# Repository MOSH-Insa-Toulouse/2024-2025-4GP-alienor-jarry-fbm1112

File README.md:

# 2024-2025-4GP - Projet Capteur low-tech Graphite - Aliénor Jarry et Bastien Maïs

## Sommaire :
- [Contexte](#contexte)
- [Livrables](#livrables)
- [Matériel nécessaire](#matériel-nécessaire)
- [1. Simulation électronique du capteur sous LTSpice](#1-simulation-électronique-du-capteur-sous-ltspice)
- [2. Design du PCB sous KiCad](#2-design-du-pcb-sous-kicad)
- [3. Réalisation du Shield](#3-réalisation-du-shield)
- [4. Code Arduino](#4-code-arduino)
- [5. Application Android APK sous MIT App Inventor](#5-application-android-apk-sous-mit-app-inventor)
- [6. Banc de test](#6-banc-de-test)
- [7. Datasheet du capteur](#7-datasheet-du-capteur)
- [Conclusion](#conclusion)
- [Contacts](#contacts)

## Contexte
Dans le cadre de l'UF "Du capteur au banc de test en open source hardware" se déroulant lors de notre 4ème année Génie Physique à l'INSA de Toulouse, nous avons développé un capteur à jauge de contrainte low-tech à base de crayon graphite. Ce projet repose sur le rapport scientifique "Pencil Drawn Strain Gauges and Chemiresistors on Paper", publié en 2014 par Cheng-Wei Lin*, Zhibo Zhao*, Jaemyung Kim & Jiaxing Huang.

Le capteur se compose uniquement d'un morceau de papier sur laquelle une trace de crayon à papier dépose une fine couche de graphite. Un dépôt de graphite sur du papier constitue un système granulaire, où des grains de tailles variables sont séparés par une distance appelée distance inter-grain. La conductance suit une loi exponentielle décroissante en fonction de la distance inter-grain, laquelle peut être modifiée en déformant le papier. Plus la distance inter-grain augmente, plus la conductance diminue. Dans ce cas, la résistance devient très élevée, car conductance et résistance sont inversement proportionnelles. Ainsi, la contrainte exercée sur le matériau peut être déterminée en mesurant simplement la résistance aux bornes du capteur.

L'objectif est de concevoir un dispositif permettant la mesure de déformation à partir d'un capteur low-tech, puis d'évaluer ses performances en le comparant à un capteur commercial.

## Livrables
- Un Shield PCB branchée sur une carte Arduino UNO, intégrant un capteur graphite, un amplificateur de transimpédance et un module Bluetooth. Idéalement, il incluerait également un écran OLED, un encodeur rotatif, un potentiomètre numérique (remplaçant la résistance R2 dans le circuit amplificateur), ainsi qu'un connecteur pour un servomoteur et un capteur de flexion (afin de comparer ses mesures avec celles du capteur en graphite).
- Un code Arduino garantissant la gestion de tous les composants et l'acquisition des mesures (mesures de contrainte, échanges via Bluetooth, affichage OLED, encodeur rotatif, potentiomètre numérique et servomoteur).
- Une application APK Android qui gère l'interface entre le PCB et le code Arduino. L'application doit au minimum afficher la valeur de la résistance de la jauge de contrainte ainsi que sa variation relative sur le smartphone.
- Un code Arduino dédié au banc de test pour la mesure de la jauge de contrainte.
- Une datasheet du capteur en graphite (incluant le circuit de transimpédance).

## Matériel nécessaire
Pour concevoir notre dispositif électronique, voici la liste des composants nécessaires :
- Des résistances : 1 de 1 kΩ, 1 de 10 kΩ, 2 de 100 kΩ pour l'amplificateur transimpédance. 1 de 47 kΩ pour le flex sensor (capteur commercial)
- Des condensateurs : 2 de 100 nF et 1 de 1 μF pour l'amplificateur transimpédance. 1 de 100 nF pour l'encodeur rotatif
- Un amplificateur opérationnel LTC1050
- Un potentiomère numérique MCP41050
- Une carte Arduino UNO
- Un module Bluetooth HC05
- Un écran OLED 128×64
- Un encodeur rotatif
- Un servomoteur
- Un flex sensor
- Un morceau de papier et crayon pour la fabrication du capteur graphite

## 1. Simulation électronique du capteur sous LTSpice

Notre capteur graphite présente une résistance variable de l’ordre du gigaohm (GΩ). Lorsque une tension de 5V est appliquée à ses bornes, un courant extrêmement faible est généré, de l’ordre de 100 nA en moyenne.

Un tel signal est difficilement exploitable sans amplification. Pour y remédier, nous avons utilisé un montage transimpédance basé sur un amplificateur opérationnel (AOP). Ce montage permet de convertir ce courant en une tension suffisamment élevée pour être lue par le convertisseur analogique-numérique (ADC) d’une carte Arduino UNO. 

**Nous avons simulé ce montage à l’aide du logiciel LTspice, voici notre schéma du circuit analogique** : 

Nous avons choisi l'AOP LTC1050 car il est adapté pour traiter de très faibles courants d'entrée. Son faible offset de tension assure une conversion précise du courant en tension.

**Deux éléments de simulation sont intégrés au circuit** :

- 🟥 Simulation du capteur  
- 🟪 Simulation du bruit

De plus, des filtres ont été ajoutés au montage afin d'atténuer les perturbations indésirables (par ex : bruits d'alimentation à 50 Hz) 

**Trois filtres assurant le traitement du signal** :

- 🟩 Filtre en entrée de l'AOP(R2, C1) :  
 C'est un filtre passe-bas passif de fréquence de coupure fc = 16 Hz. Il filtre les bruits en courant sur le signal d'entrée.

- 🟦Filtre couplé à l'AOP (R4, C2) :  
  C'est un filtre passe-bas actif avec fc = 1,6 Hz. Il filtre la composante du bruit à 50Hz du réseau électrique.

- 🟨 Filtre en sortie de l'AOP (R5, C4) :  
  C'est un filtre passe-bas passif avec fc = 1,6 kHz. Il élimine les parasites générés lors du traitement du signal.

De plus, la résistance R1 en entrée protège contre les décharges électrostatiques. Cette résistance en combinaison avec la capacité C5, forme un filtre pour atténuer les bruits de tension. 

**Voici la réponse de notre circuit afin de vérifier que le capteur est bien amplifié** :

Nous voyons que le signal est amplifié à 1V. Ainsi, l'Arduino UNO pourra le mesurer. 

**Réponse avec un courant alternatif pour vérifier que le bruit est bien filtré** :

Nous remarquons que le bruit est bien atténué à 50 Hz, d'environ 72 dB.

## 2. Design du PCB sous KiCad

Notre PCB a été conçue sur le logigiel Kicad (version 9).

Nous avons tout d'abord réalisé la schématique en reproduisant le circuit transimpédance (en enlevant la partie simulant le bruit). Nous avons  remplacé la résistance R3 par un potentiomètre digital. Cela nous permet d'ajuster le gain de notre AOP en fonctions de nos besoins. Également, nous avons créé les symboles des différents composants/modules intégrés. Ces modules assureront une mesure précise de notre capteur en graphite et permettra de comparer les résultats obtenus.

**Voici le schéma électrique de l'ensemble de notre montage** :

Ensuite, nous avons réalisé les empreintes de nos composants en prenant en compte leurs caractéristiques techniques : nombre de pins, espacement, dimensions, géométrie,...
afin de les placer sur notre PCB. 

Puis, nous sommes allés dans l'onglet "éditeur de PCB" sous Kicad pour designer notre circuit. Nous nous sommes appuyés sur un modèle de carte Arduino Uno. Nous avons ainsi placé nos différents composants, de manière à regouper les composants du circuit transmpédance. De plus les modules, et les composants du circuit transimpédance devaient être placés proches de leurs branchements Arduino respectifs. Nous sommes ensuite passés à la partie routage du circuit. Notre principale difficulté a été d’optimiser le placement des composants afin de limiter au maximum l’utilisation de vias, notamment pour les connexions au GND. Nous avons tout de même trois vias sur notre PCB. Pour garantir une bonne connexion entre toutes les broches GND des composants, nous avons mis en place un plan de masse.

**Voici le résultat final obtenu de notre routage** : 

**Voici le rendu 3D de notre PCB, avec ses différents modules et composants intégrés**:

### **Erreurs réalisées** : 

Nous avons fait quelques erreurs concernant les empreintes de nos modules.

**Servomoteur** :
Nous avons inversé les broches GND et 5V. 

**Bluetooth HC-05** : 
L'empreinte de notre Bluetooth n'est pas correcte. Nous avions mis dans l'ordre la broche VCC, GND, TX, RX, ENABLE et STATE alors que la broche ENABLE est la première. Voici les broches correctes du Bluetooth :

Un conseil serait de se baser sur la datasheet de chaques composant afin de réaliser les empreintes! De plus, il faut faire attention concerant les broches TX et RX du Bluetooth. La broche RX de la carte Arduino doit être raccordée à la broche TX du Bluetooth, et la broche TX du Arduino à la broche RX du Bluetooth.
Nous avons résolu le problème des pins Bluetooth en utilisant des connecteur mâles, femelles permettant de brancher correctement le Bluetooth.

## 3. Réalisation du Shield 

Une fois notre PCB finalisé sous KiCad, nous l’avons envoyé à Cathy afin qu’elle puisse vérifier que le PCB était conforme et prêt pour une impression correcte. Puis, nous avons généré le masque de gravure de notre PCB que Cathy s’est chargée d’imprimer. Ensuite, nous sommes allées avec Cathy au GEI afin de tirer notre PCB.

Nous n’avons pas pu manipuler directement, mais nous avons tout de même pu observer le processus de fabrication de la carte. Cathy a procédé ainsi :

1. Insolation UV de la plaque en époxy recouverte d'une fine couche de cuivre (destinée à recevoir le circuit imprimé) et d'une résine photosensible, à travers le masque, pour durcir la résine dans les zones exposées.
2. Développement : la plaque est plongée dans un révélateur pour éliminer la résine non exposée à la lumière UV, laissant ainsi un motif de résine durcie correspondant au circuit imprimé.
3. Gravure : La plaque est ensuite immergée dans un bain de perchlorure de fer, qui dissout le cuivre non protégé par la résine durcie, formant ainsi les pistes du circuit imprimé.
4. Nettoyage à l’acétone pour éliminer les résidus de résine restants après la gravure.

**Voici une photo du masque de gravure et une photo de notre PCB une fois imprimé** :

**Nous tenions à grandement remercier Cathy pour son aide tout au long du projet, et en particulier pour l'impression de notre PCB.**

### Assemblage du circuit :

Nous avons ensuite procédé au perçage de la plaquette pour permettre l'insertion des différents composants, en veillant à respecter la taille des trous. Un forêt plus petit était nécessaire pour les résistances et les condensateurs. Une fois le perçage effectué, nous avons soudé les composants sur le PCB. Il faut bien faire attention à souder uniquement sur les pastilles, sauf pour les pastilles GND où un débordement est moins problématique, car elles sont toutes reliées au plan de masse. Un excès de soudure sur les pastilles pourrait en effet créer des courts-circuits. De plus, nous avons dû ajouter un fil reliant la broche 5V du flex sensor au 5V du module Bluetooth, car une portion de cuivre sur la piste les reliant a été retirée accidentellement en tentant d’enlever un surplus de soudure.

**Voici une photo de l'assemblage de notre circuit (sans les modules) ainsi qu'une photo de nos soudures** :

## 4. Code Arduino 

Afin de réaliser le code arduino nous avons utilisé l'IDE 2.3.2.

Dans le cadre d'une utilisation d'application mobile nous avons donc utilisé un module bluetooth. Cela a ainsi nécessité d'inclure la librairie SoftwareSerial pour initier la communication entre l'application et le pcb via le module.

Pour une utilisation plus classique de notre montage, l'écran OLED permet l'affichage des valeurs issues des mesures de capteurs de la plaquette impliquant l'utilisation de la librairie Adafruit_SSD1306. Cette librairie est plus délicate à manipuler car gourmande en mémoire RAM. Pour pallier cet effet, il nous est impératif de limiter l'affichage au strict nécessaire afin de contrôler l'utilisation de la RAM et d'éviter d'éventuels disfonctionnements du programme.

Dans le dossier Arduino se trouve le programme complet strucuré qui permet de faire différents types de mesures selon le capteur utilisé (graphite ou flex sensor). Lors du lancement de l'Arduino, le programme effectue une calibration du potentiomètre digital selon la valeur mesurée par le capteur graphite pour ensuite afficher un menu déroulant que l'on peut balayer à l'aide de l'encodeur rotatif.

Le menu affiche 3 choix d'actions possibles : 

- Une mesure instantanée du capteur graphite toutes les 500ms
- Une mesure du flex sensor toutes les 500ms
- Une calibration du potentiomètre digital

Pour sélectionner une action du menu, il suffit de tourner la molette et d'appuyer sur le bouton central de l'encodeur. Si l'on souhaite sortir d'une action du menu, nous tournons simplement la molette de l'encodeur.

Ainsi, on obtient la résistance du capteur graphite avec la formule suivante :

Et dans notre cas, notre résistance R3 est variable : elle est issue du réglage du potentiomètre à l'aide d'une méthode de dichotomie.

Finalement, nous n'avons pas utilisé le servomoteur comme module par manque de temps.

## 5. Application Android APK sous MIT App Inventor
Comme mentionné dans la partie précèdente, une application mobile a été réalisée sous MIT App Inventor.
L'application reçoit les données transmis par le module bluetooth HC-05 puis affiche la valeur reçue en Mohm pour le capteur graphite ou en ohms pour le flex sensor.

## 6. Banc de test
Pour spécifier notre capteur graphite et son montage transimpédance, nous avons utilisé le banc de test fabriqué par le binôme Maëlys et Arthur. Un grand merci à eux de nous avoir prêter leur banc de test. Ce banc de test comporte des demis-cercles avec des diamètres différents allant de 2cm à 4,5cm avec un rajout de 0,5cm entre chaque demi-cercle. Au total, il y a 6 demi-cercles. Ce banc de test comporte des encoches pour chaque demi-cercle qui permet d'insérer facilement le capteur. Une fois le capteur mis dans l'une de ses encoches, il est plus aisé d'appliquer une flexion ou une compression sur le capteur. La capteur se déforme en suivant la courbure du demi-cercle. Ainsi, nous appliquons une contrainte qui provoque une variation de la résistance du capteur. Nous allons mesurer cette contrainte en fonction de la déformation.

La variation relative de la résistance se définit par : ΔR/R0 (avec R0 la résistance initiale du capteur avant sa déformation et ΔR la variation de la résistance après et avant déformation). La déformation est : ε=e/D (avec e=0,2mm l'épaisseur du papier utilisé et D le diamètre du demi-cercle). Nous avons donc une déformation variant de 0.004 pour le plus grand demi-cerle à 0.01 pour le plus petit. Il faut faire attention à bien mettre les diamètres des demi-cercles en mm! 

**Voici le banc de test que nous avons utilisé :**

### Voici les courbes caractéristiques pour des crayons F, HB et B en flexion et en compression :

### Voici le graphe comparant le Flex Sensor et le capteur Graphite pour F, HB et B (en flexion) :

**Interprétation des courbes et comparaison avec la théorie :**

Nous remarquons que la résistance augmente lorsque nous mettons le capteur en flexion et que la résistance diminue lors de la compression de ce dernier. Ce phénomène est tout à fait attendu : en théorie, lorsqu’on soumet le capteur à une flexion, la monocouche de graphite déposée sur le papier s’étire, augmentant la distance entre les atomes de carbone. Cette augmentation de distance entraîne une hausse de la résistance du capteur. À l’inverse, en compression, les atomes de carbone se rapprochent, entraînant une diminution de la résistance.

Nous remarquons que les variations relatives ne sont pas les mêmes en fonction de la dureté du crayon utilisé. 
Plus le crayon est gras :  9H<...<3H<2H<H<F<HB<B<2B<3B<...9B, moins sa variation relative de résistance est élevée.
Dans notre cas, le crayon le plus dur et le crayon de type F et le plus gras est celui de type B. 
Cette théorie est vérifiée pour le cas des courbes en compression. Nous voyons bien que le type F a la variation relative la plus élevée et le B, la variation la moins élevée.
Pour le cas des courbes en flexion, la théorie n'est pas totalement vérifiée car le type F a bien la variation de résistance la plus élevée. Cependant, la variation relative la moins élevée est le type HB, alors que cela devrait être le type B. De plus, nous remarquons que nos courbes F, aussi bien en flexion qu'en compression présente un comportement non linéaire marqué. Ces courbes montrent plusieurs irrégularités et pics contrairement aux courbes de type B et HB qui sont plus linéaires.

Ces erreurs expérimentales peuvent être dues à une certaine instabilité dans la réponse du capteur, possiblement liée à une mauvaise homogénéité du dépôt de graphite. Elles peuvent également provenir de la qualité des crayons, des microfissures dans la couche conductrice (lors de la déformation mécanique) ou encore d'un contact imparfait entre le graphite et les pinces.

**Comparaison entre le capteur graphite et le capteur Flex sensor commercial :**

Enfin, nous avons comparé notre capteur graphite avec un flex sensor commercial. Ce flex sensor ne peut se déformer qu'en flexion (et non en compression). De plus, nous n'avons pas pu déformer le flex sensor à l'aide du plus petit demi-cercle de diamètre 20mm. En effet, les pins femelles du flex sensor sont directement fixés sur la PCB, ce qui  a limité la flexibilité du flex sensor. Pour avoir le même nombre de points sur le graphe que le flex sensor, nous n'avons donc pas pris en compte le plus petit demi-cercle pour le F, HB et B. Ceci explique la différence de pente pour le F, HB et B entre ce graphe et le premier graphe. 

Le flex sensor a une variation relative très élevée avec une pente a environ 180 comparé au capteur graphite, où la pente est de l'ordre de 20 à 60. Le capteur Flex est donc beaucoup plus sensible à la déformation. Sa réponse est plus régulière, linéaire et plus exploitable en conditions réelles.

## 7. Datasheet du capteur
Vous pouvez consulter la datasheet de notre capteur [ici](GSS250_Technical_Datasheet_Official.pdf).

## Conclusion
Malgré la composante low cost et de facilité d'usage de notre capteur, son nombre d'utilisation est très limité, qui diminue pour une déformation élevée.
En comparaison le Flex Sensor est plus sensible à la déformation avec un signal de réponse plus régulier est continu.

La mise en place du capteur graphite dans l'industrie amène aussi une contrainte de contrôle des épaisseurs du graphène sur le papier de manière homogène. En effet, les conditions d'essai sont non reproductibles car la quantité de graphite déposée au crayon à papier (à la main) variable, induisant ainsi une résistance variable à son tour. Les méthodes de dépot de couches actuels amène ainsi des couts suplémentaires

Tout de même, sa conception fait que l'on peut mesurer des tensions et des compressions avec un même produit.

Aussi, à l'issue du banc de test, nous avons retenu qu'il faudrait parvenir à un meilleur système de mise sous contraintes. Les manipulations manuelles requierent d'être suffisament alerte afin d'éviter des déformations additionelles au capteur limitant son utilisation. L'implémentaion de l'installation avec un servo moteur est une piste à suivre tout comme des pin plus adapté aux cables de connexion du capteur sur le pcb.

## Contacts
Aliénor Jarry : [ajarry@insa-toulouse.fr](mailto:ajarry@insa-toulouse.fr)  
Bastien Maïs : [mais@insa-toulouse.fr](mailto:mais@insa-toulouse.fr)

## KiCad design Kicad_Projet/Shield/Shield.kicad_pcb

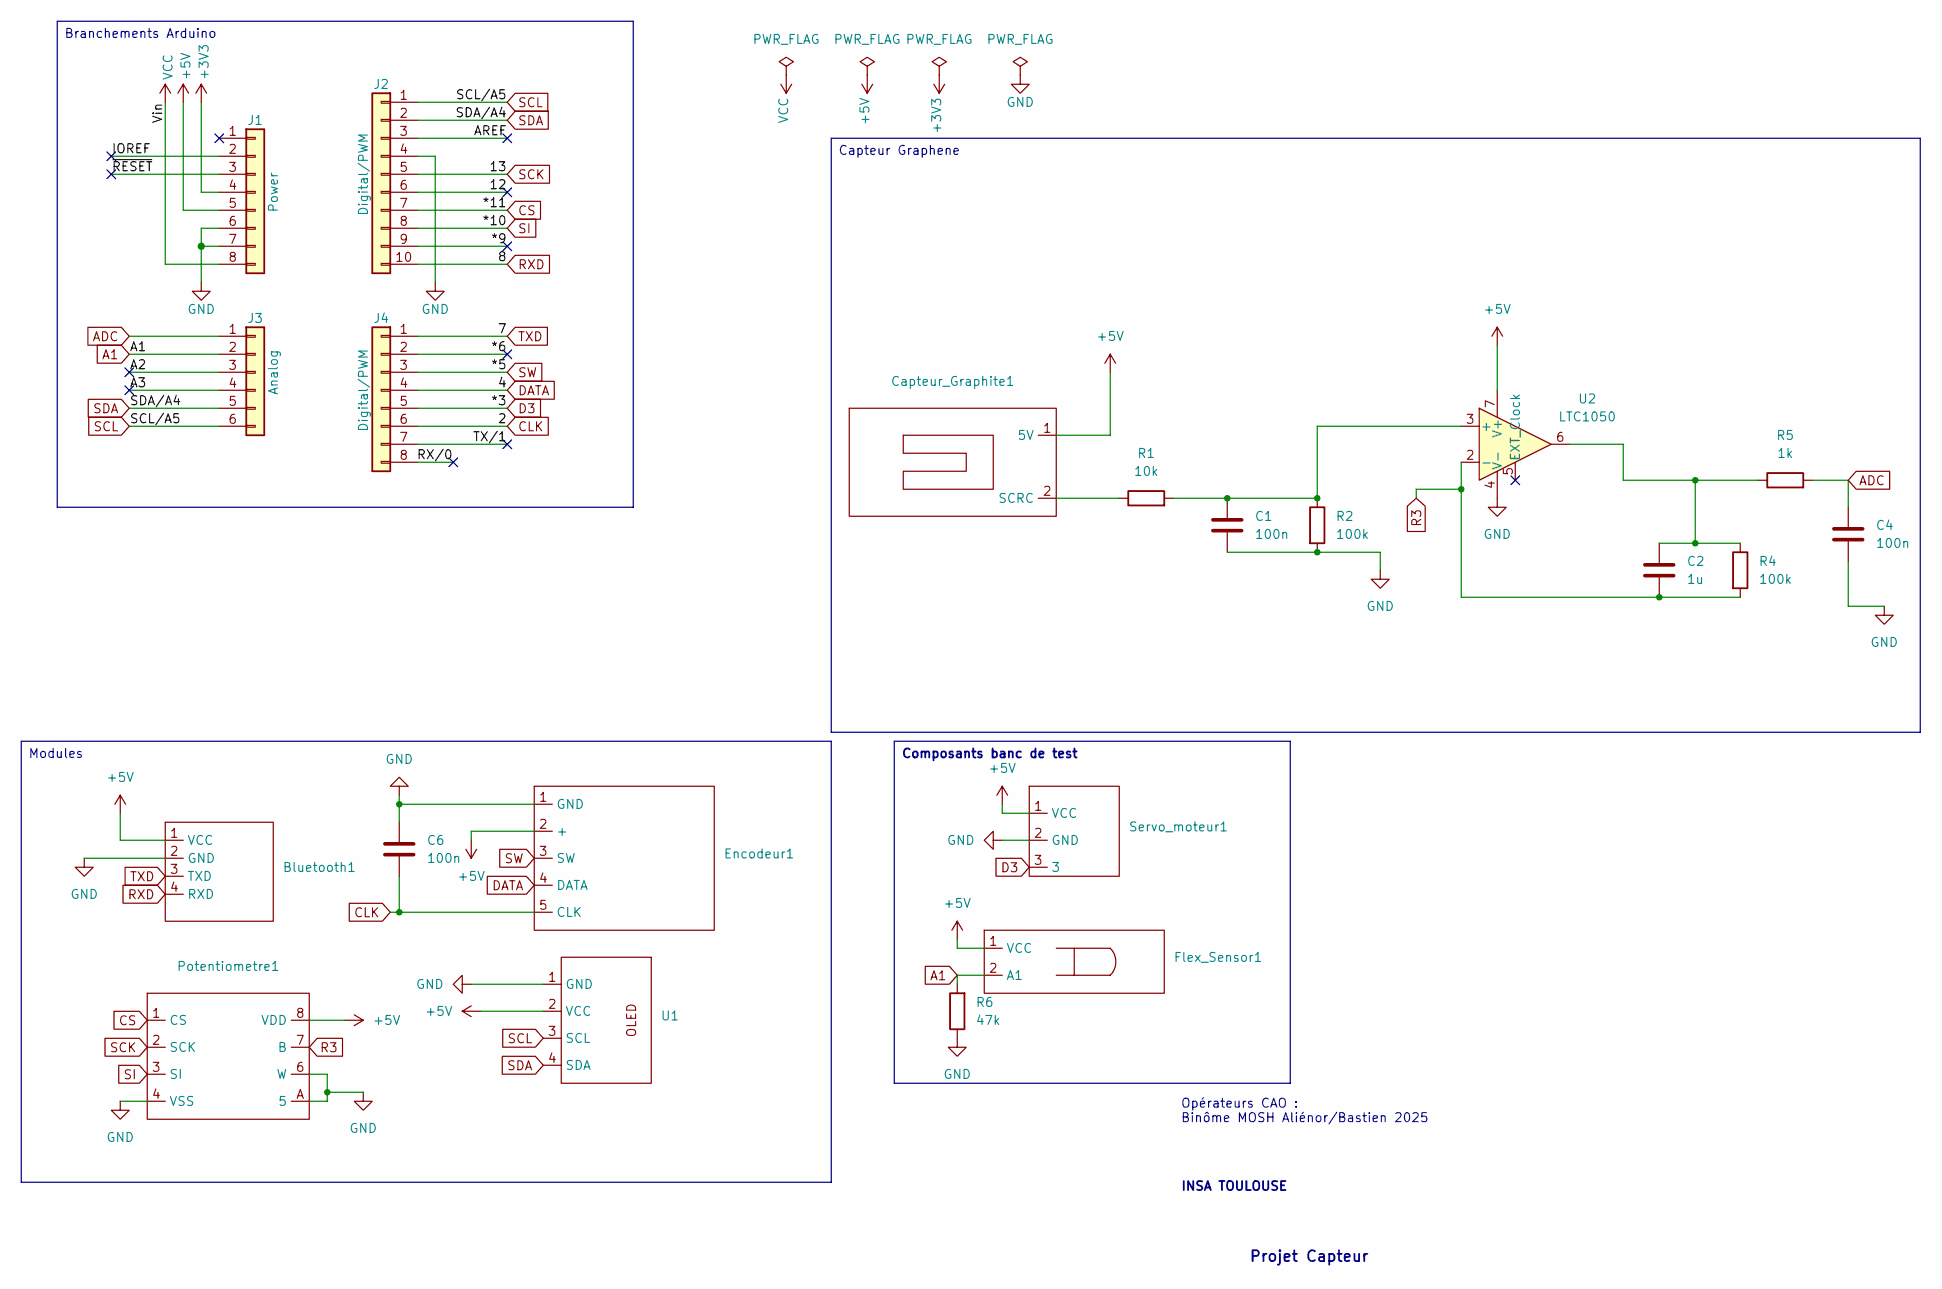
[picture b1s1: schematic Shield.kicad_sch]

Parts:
Bluetooth1: Bluetooth
C1, C4, C6: 100n; C_Disc_D4.3mm_W1.9mm_P5.00mm
C2: 1u; C_Rect_L7.0mm_W4.5mm_P5.00mm
Capteur_Graphite1: Capteur
Encodeur1: Encodeur
Flex_Sensor1: Flex_Sensor
J1: Power; PinSocket_1x08_P2.54mm_Vertical
J2: Digital/PWM; PinSocket_1x10_P2.54mm_Vertical
J3: Analog; PinSocket_1x06_P2.54mm_Vertical
J4: Digital/PWM; PinSocket_1x08_P2.54mm_Vertical
Potentiometre1: Potentiometre
R1: 10k; R_Axial_DIN0207_L6.3mm_D2.5mm_P10.16mm_Horizontal
R2, R4: 100k; R_Axial_DIN0207_L6.3mm_D2.5mm_P10.16mm_Horizontal
R5: 1k; R_Axial_DIN0207_L6.3mm_D2.5mm_P10.16mm_Horizontal
R6: 47k; R_Axial_DIN0207_L6.3mm_D2.5mm_P10.16mm_Horizontal
Servo_moteur1: Servo_Moteur
U1: OLED
U2: LTC1050; Ampli

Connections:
+3V3: J1.4
+5V: Bluetooth1.1 (VCC), Capteur_Graphite1.1 (5V), Encodeur1.2 (+), Flex_Sensor1.1 (VCC), J1.5, Potentiometre1.8 (VDD), Servo_moteur1.1 (VCC), U1.2 (VCC), U2.7 (V+)
/12: J2.6
/*6: J4.2
/*9: J2.9
/A2: J3.3
/A3: J3.4
/AREF: J2.3
/IOREF: J1.2
/RX/0: J4.8
/TX/1: J4.7
/~RESET: J1.3
A1: Flex_Sensor1.2 (A1), J3.2, R6.2
ADC: C4.1, J3.1, R5.2
CLK: C6.2, Encodeur1.5 (CLK), J4.6
CS: J2.7, Potentiometre1.1 (CS)
D3: J4.5, Servo_moteur1.3
DATA: Encodeur1.4 (DATA), J4.4
GND: Bluetooth1.2 (GND), C1.2, C4.2, C6.1, Encodeur1.1 (GND), J1.6, J1.7, J2.4, Potentiometre1.4 (VSS), Potentiometre1.6 (W), Potentiometre1.A (5), R2.2, R6.1, Servo_moteur1.2 (GND), U1.1 (GND), U2.4 (V-)
unnamed: C2.1, R4.1, R5.1, U2.6
unnamed: Capteur_Graphite1.2 (SCRC), R1.1
unnamed: C1.1, R1.2, R2.1, U2.3 (+)
R3: C2.2, Potentiometre1.7 (B), R4.2, U2.2 (-)
RXD: Bluetooth1.4 (RXD), J2.10
SCK: J2.5, Potentiometre1.2 (SCK)
SCL: J2.1, J3.6, U1.3 (SCL)
SDA: J2.2, J3.5, U1.4 (SDA)
SI: J2.8, Potentiometre1.3 (SI)
SW: Encodeur1.3 (SW), J4.3
TXD: Bluetooth1.3 (TXD), J4.1
VCC: J1.8

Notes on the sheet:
Opérateurs CAO : Binôme MOSH Aliénor/Bastien 2025
Projet Capteur
INSA TOULOUSE
Composants banc de test
Branchements Arduino
Modules
Capteur Graphene

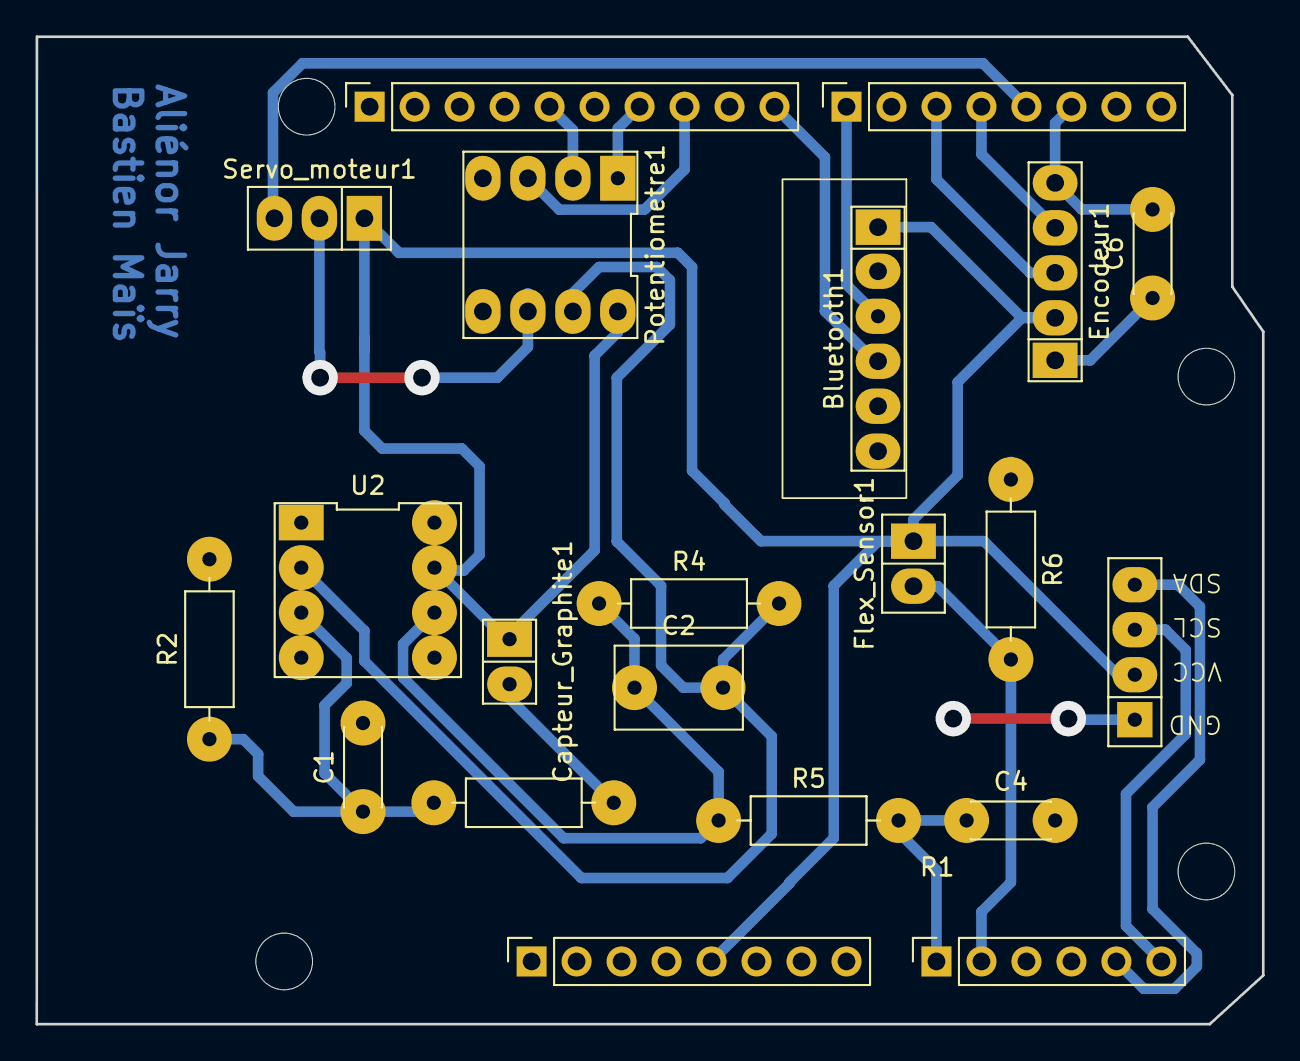
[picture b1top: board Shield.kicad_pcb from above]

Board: 2 copper layers, 69.2 x 55.8 mm, 25 parts (0 on the bottom side), 19 nets.

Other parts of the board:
MH1, MH2, MH3, MH4: MountingHole_3.2mm

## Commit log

2025-02-21 Ajout de ma to do liste
2025-02-21 Ajout d'un item à ma liste
2025-02-21 test
2025-03-24 connectique
2025-03-24 connectique suite
2025-03-24 Routage_V1
2025-03-25 routage_V2
2025-03-25 test5
2025-03-25 pcb and mask
2025-05-07 Create Images
2025-05-07 Create fichierA
2025-05-13 Create aaaaa
2025-05-20 Create cc
2025-05-20 Create hello
